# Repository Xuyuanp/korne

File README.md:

# Korne

| left                           | right                        |
| ------------------------------ | ---------------------------- |
|  |  |

## Features

- Declarative layout configuration (powered by ergogen)
- Reversible PCB design
- Nice!View support (not tested yet)
- Wireless only
- 3D printed magnetic cases
- Compatible with ZMK firmware of Corne
- The staggered layout fits my hands perfectly

## Credits

- [Ergogen](https://github.com/ergogen/ergogen)
- [ErgoPad](https://pashutk.com/ergopad/)
- [Flatfoot Fox's awesome blog](https://flatfootfox.com/ergogen-introduction/)
- [samoklava](https://github.com/soundmonster/samoklava)
- [infused-kim's footprints
](https://github.com/infused-kim/kb_ergogen_fp)

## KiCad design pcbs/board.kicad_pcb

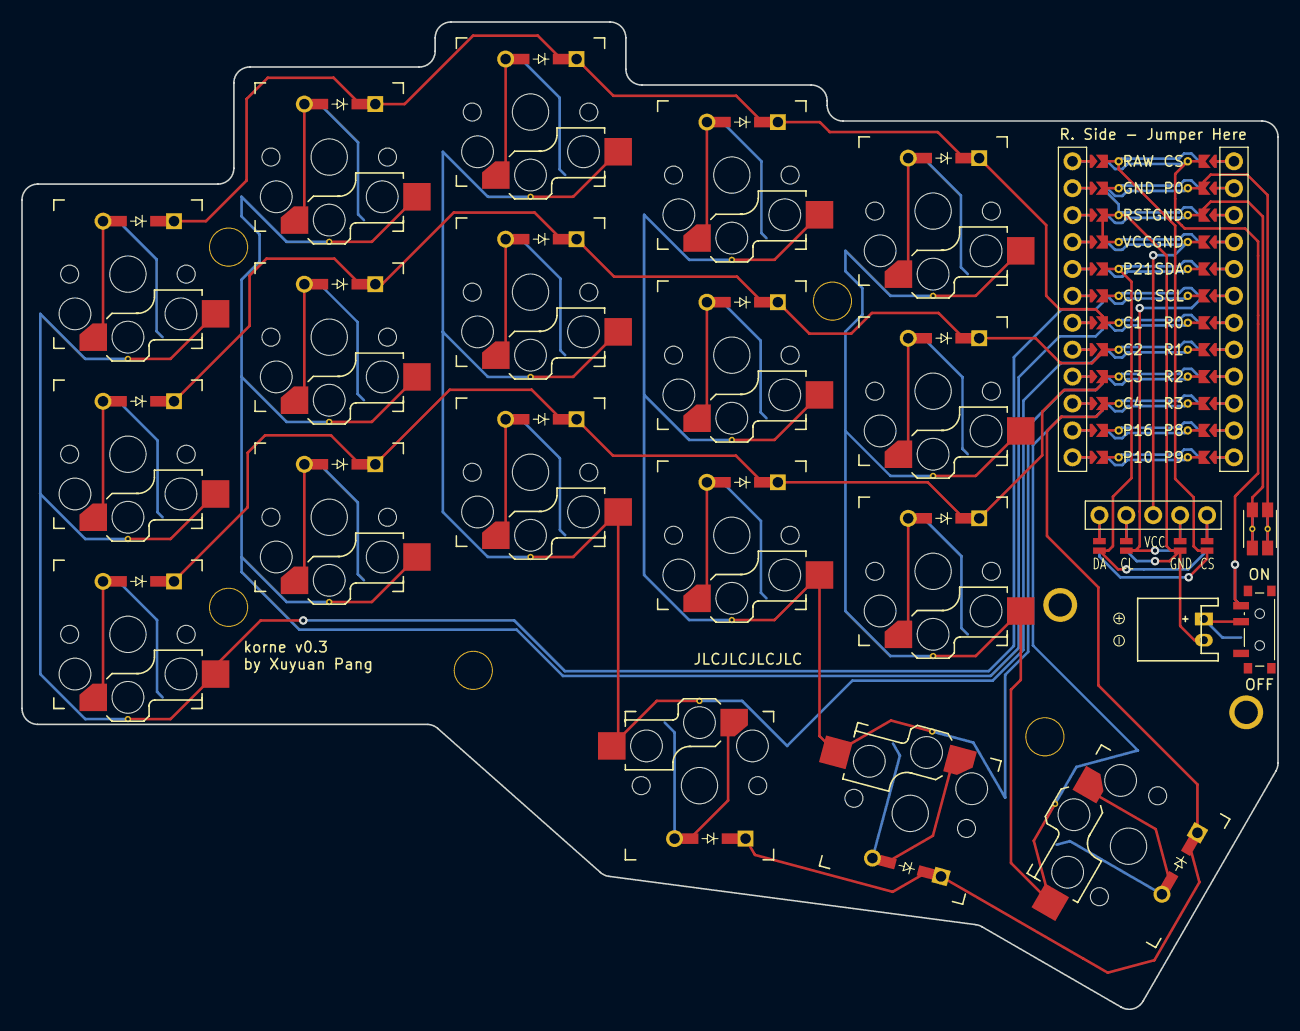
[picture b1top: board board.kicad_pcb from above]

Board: 2 copper layers, 118.6 x 93.2 mm, 49 parts (0 on the bottom side), 39 nets.

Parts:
D1, D2, D3, D4, D5, D6, D7, D8, D9, D10, D11, D12, D13, D14, D15, D16, D17, D18: ComboDiode
DISP1: nice!view
H1, H2, H3, H4, H5, H6, H7: mounting_hole
ICON1: icon_bat
JST1: JST_PH_S2B-PH-K_02x2.00mm_Angled
MCU1: nice_nano
S1, S2, S3, S4, S5, S6, S7, S8, S9, S10, S11, S12, S13, S14, S15, S16, S17, S18: PG1350
SW1: sw_reset_side
SW2: power_switch

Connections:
BAT+: JST1.1, SW2.2, SW2.5
CS: DISP1.13, DISP1.23, MCU1.124
DISP1_1: DISP1.1, DISP1.14, DISP1.27
DISP1_2: DISP1.2, DISP1.15, DISP1.26
DISP1_4: DISP1.4, DISP1.16, DISP1.25
DISP1_5: DISP1.5, DISP1.17, DISP1.24
GND: DISP1.12, DISP1.22, JST1.2, MCU1.2, MCU1.121, MCU1.122, SW1.2
MOSI: DISP1.10, DISP1.20, MCU1.120
RAW: MCU1.1, SW2.3, SW2.6
RST: MCU1.3, SW1.1
SCK: DISP1.11, DISP1.21, MCU1.119
VCC: DISP1.3, MCU1.4
col_index: MCU1.9, S10.2, S11.2, S12.2, S16.2
col_inner: MCU1.10, S13.2, S14.2, S15.2, S18.2
col_middle: MCU1.8, S7.2, S8.2, S9.2, S17.2
col_pinky: MCU1.6, S1.2, S2.2, S3.2
col_ring: MCU1.7, S4.2, S5.2, S6.2
far_thumb: D16.2, S18.1
home_thumb: D17.2, S16.1
index_bottom: D10.2, S10.1
index_home: D11.2, S11.1
index_top: D12.2, S12.1
inner_bottom: D13.2, S13.1
inner_home: D14.2, S14.1
inner_top: D15.2, S15.1
middle_bottom: D7.2, S7.1
middle_home: D8.2, S8.1
middle_top: D9.2, S9.1
near_thumb: D18.2, S17.1
pinky_bottom: D1.2, S1.1
pinky_home: D2.2, S2.1
pinky_top: D3.2, S3.1
ring_bottom: D4.2, S4.1
ring_home: D5.2, S5.1
ring_top: D6.2, S6.1
row_bottom: D1.1, D4.1, D7.1, D10.1, D13.1, MCU1.116
row_home: D2.1, D5.1, D8.1, D11.1, D14.1, MCU1.117
row_thumb: D16.1, D17.1, D18.1, MCU1.115
row_top: D3.1, D6.1, D9.1, D12.1, D15.1, MCU1.118

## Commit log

2023-12-10 points
2023-12-10 outlines
2023-12-10 lock
2023-12-11 updated outlines
2023-12-11 fix thumbfan overlap
2023-12-11 improved pcbs
2023-12-11 checkout submodules
2023-12-11 removed switch solder holes
2023-12-11 adjust diode
2023-12-11 update jst
2023-12-11 removed jst
2023-12-11 rotate reset button
2023-12-11 added right promicro
2023-12-11 restore jstph
2023-12-12 added makefile
2023-12-12 relocated footprints
2023-12-12 added submodule samoklava
2023-12-12 added helper points
2023-12-12 try removed switches
2023-12-13 fixed niceview label
2023-12-13 added mounting_holes added silks reverse nice view's jumper
2023-12-14 added mcu cover mounting holes
2023-12-14 added top case
2023-12-15 added outline templates
2023-12-17 updated pcbs and cases
2023-12-17 feat(cases): added magnet slots
2023-12-17 feat(cases): added rubber feet
2023-12-17 added pcbs and cases
2023-12-17 removed actions
2023-12-17 feat(cases): updated bottom case
2023-12-17 chore: updated makefile
2023-12-17 chore: added pcb preview images
2023-12-17 chore: updated pcb images
2023-12-20 feat(points): updated thumbfan layout
2023-12-23 feat(pcbs): more compact
2023-12-23 feat(pcbs): customized diode
2023-12-23 feat(pcbs): updated jlc maker
2023-12-23 feat(pcbs): adjust mcu cover screw holes
2023-12-24 feat(cases): added switch notch
2023-12-24 feat(cases): added usb-c notch
2023-12-24 feat(cases): added standoff roots
2023-12-24 feat(cases): added pcb supports
2023-12-24 feat(cases): cleanup unused outlines
2023-12-24 feat(cases): adjust rubbers
2023-12-24 feat(pcbs,cases): removed vertical padding
2023-12-24 feat(cases): adjust pcb supports
2023-12-24 feat(chore): updated version
2023-12-24 chore: release v0.2
2023-12-27 feat(outlines): added preview outline
2023-12-29 feat(cases): added preview 3d model
2023-12-29 feat(points): adjust thumb cluster keys
2023-12-30 feat(pcbs): swap net of reset switch
2023-12-30 feat(pcbs): rotate switches
2023-12-30 chore: new version
2023-12-30 feat(cases): make mirrord cases
2024-01-02 feat(cases): improved mountings
2024-01-03 feat(pcbs): added routed v0.3 pcb
2024-01-04 feat(pcbs): adjust traces & updated preview images
2024-01-04 feat(pcbs): added gerbers
2024-01-05 feat(pcbs): updated preview images
2024-01-05 chore: updated readme
2024-01-06 feat(pcbs): updated keycaps size
2024-01-07 feat(cases): adjust bottom screw holes
2024-01-13 feat(pcbs): updated pcb keycaps preview
2024-01-13 feat(cases): adjust bottom wall
2024-01-17 feat(pcbs): improved pcb display
2024-12-16 mini version
2024-12-20 relocated matrix and thumbfan
2024-12-20 refactor pcb
2024-12-20 chore: format
2024-12-20 chore: upgraded ergogen for kicad8 and aggregate.intersect
2024-12-20 feat(pcb): updated net
2024-12-26 feat: used ceoloide's footprints
2024-12-26 feat(pcbs): added 3d modules
2024-12-26 feat(pcbs): updated power and jstph
